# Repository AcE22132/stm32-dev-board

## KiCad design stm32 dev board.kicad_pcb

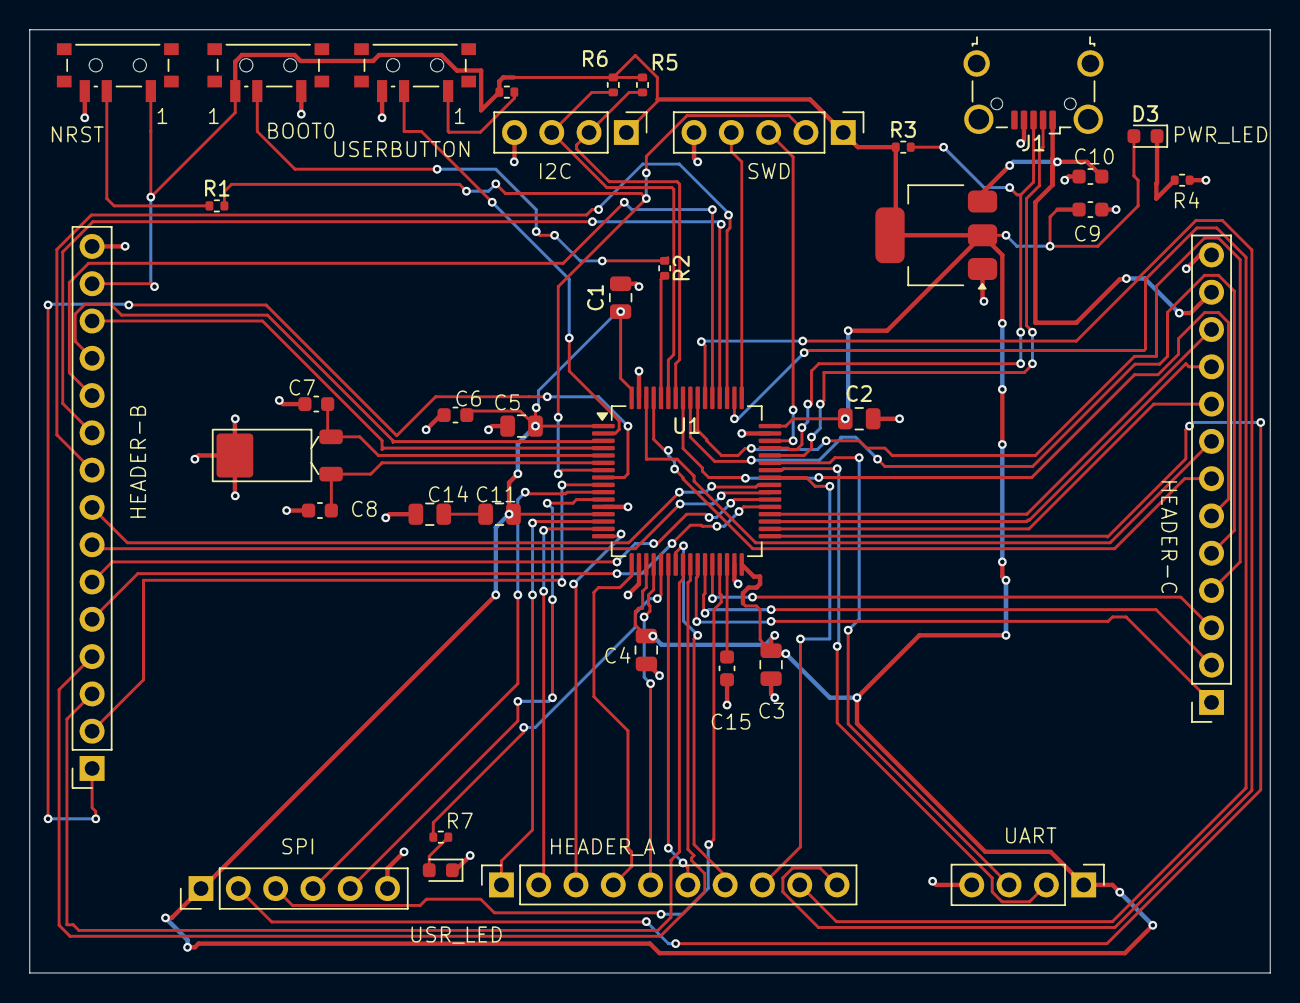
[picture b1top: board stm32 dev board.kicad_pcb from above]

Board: 2 copper layers, 84.5 x 64.2 mm, 37 parts (0 on the bottom side), 62 nets.

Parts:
C1, C2, C3, C4, C5, C11: 100n; C_0805_2012Metric
C6: 10u; C_0603_1608Metric
C7: 5p; C_0603_1608Metric
C8: 5pf; C_0603_1608Metric
C9, C10: 22u; C_0603_1608Metric
C14: 1u; C_0805_2012Metric
C15: 2.2u; C_0603_1608Metric
D2, D3: LED; LED_0603_1608Metric
J1: USB_B; USB_Micro-B_Wuerth_629105150521_CircularHoles
J2: Conn_01x05_Pin; PinHeader_1x05_P2.54mm_Vertical
J3, J4: Conn_01x04_Pin; PinHeader_1x04_P2.54mm_Vertical
J5: Conn_01x15_Socket; PinSocket_1x15_P2.54mm_Vertical
J6: Conn_01x13_Socket; PinSocket_1x13_P2.54mm_Vertical
J8: Conn_01x06_Pin; PinHeader_1x06_P2.54mm_Vertical
J9: Conn_01x10_Socket; PinSocket_1x10_P2.54mm_Vertical
R1, R2: 10k; R_0402_1005Metric
R3, R4, R5, R6, R7, R8: 1k5; R_0402_1005Metric
SW1, SW2, SW3: SW_Push_SPDT; SW_SPDT_PCM12
U1: STM32F401RET6; LQFP-64_10x10mm_P0.5mm
U2: AMS1117-3.3; SOT-223-3_TabPin2
Y1: Crystal_GND3; Crystal_SMD_FrontierElectronics_FM206

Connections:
+3.3V: C1.1, C2.1, C3.1, C4.1, C5.1, C6.1, C9.1, C11.2, D3.2 (A), J2.1, J3.1, J4.1, J5.14, J8.1, R3.1, R5.1, R6.1, R8.1, SW1.1 (A), SW2.3 (C), U1.1 (VBAT), U1.13 (VREF+), U1.19 (VDD), U1.32 (VDD), U1.48 (VDD), U1.64 (VDD), U2.2 (VO)
+5V: C10.1, J1.1 (VBUS), J6.12, U2.3 (VI)
/NRST: J2.2, R1.2, U1.7 (NRST)
/SPI_MISO: J8.4, U1.10 (PC2)
/SPI_MOSI: J8.5, U1.11 (PC3)
/SPI_NSS: J8.2, U1.33 (PB12)
/SPI_SCK: J8.3, U1.29 (PB10)
/pa0: J9.1, U1.14 (PA0)
/pa1: J9.2, U1.15 (PA1)
/pa2: J9.3, U1.16 (PA2)
/pa3: J9.4, U1.17 (PA3)
/pa4: J9.5, U1.20 (PA4)
/pa6: J9.6, U1.22 (PA6)
/pa7: J9.7, U1.23 (PA7)
/pa8: J9.8, U1.41 (PA8)
/pa15: J9.9, U1.50 (PA15)
/pb0: J6.1, U1.26 (PB0)
/pb1: J6.2, U1.27 (PB1)
/pb2: J6.3, U1.28 (PB2)
/pb3: J6.4, U1.55 (PB3)
/pb4: J6.5, U1.56 (PB4)
/pb5: J6.6, U1.57 (PB5)
/pb8: J6.7, U1.61 (PB8)
/pb9: J6.8, U1.62 (PB9)
/pb13: J6.9, U1.34 (PB13)
/pb14: J6.10, U1.35 (PB14)
/pb15: J6.11, U1.36 (PB15)
/pc0: J5.1, U1.8 (PC0)
/pc1: J5.2, U1.9 (PC1)
/pc4: J5.3, U1.24 (PC4)
/pc5: J5.4, U1.25 (PC5)
/pc6: J5.5, U1.37 (PC6)
/pc7: J5.6, U1.38 (PC7)
/pc8: J5.7, U1.39 (PC8)
/pc9: J5.8, U1.40 (PC9)
/pc10: J5.9, U1.51 (PC10)
/pc11: J5.10, U1.52 (PC11)
/pc12: J5.11, U1.53 (PC12)
/pc14: J5.12, U1.3 (PC14)
/pc15: J5.13, U1.4 (PC15)
/pd2: J9.10, U1.54 (PD2)
GND: C1.2, C2.2, C3.2, C4.2, C5.2, C6.2, C7.2, C8.2, C9.2, C10.2, C14.1, C15.1, D2.1 (K), J1.4 (GND), J2.5, J3.4, J4.4, J5.15, J6.13, J8.6, R4.2, SW1.3 (C), SW2.1 (A), SW3.3 (C), U1.12 (VSSA), U1.18 (VSS), U1.31 (VSS), U1.47 (VSS), U1.63 (VSS), U2.1 (GND), Y1.3
unnamed: C11.1, C14.2
unnamed: D2.2 (A), R7.1
unnamed: D3.1 (K), R4.1
unnamed: J1.3 (D+), R3.2, U1.45 (PA12)
unnamed: J1.2 (D-), U1.44 (PA11)
unnamed: J2.3, U1.46 (PA13)
unnamed: J2.4, U1.49 (PA14)
unnamed: J3.2, U1.42 (PA9)
unnamed: J3.3, U1.43 (PA10)
unnamed: J4.2, R5.2, U1.58 (PB6)
unnamed: J4.3, R6.2, U1.59 (PB7)
unnamed: R1.1, SW1.2 (B)
unnamed: R2.1, SW2.2 (B)
unnamed: R8.2, SW3.1 (A)
unnamed: SW3.2 (B), U1.2 (PC13)
unnamed: R2.2, U1.60 (BOOT0)
unnamed: R7.2, U1.21 (PA5)
unnamed: C7.1, U1.5 (PH0), Y1.1
unnamed: C8.1, U1.6 (PH1), Y1.2
unnamed: C15.2, U1.30 (VCAP1)
